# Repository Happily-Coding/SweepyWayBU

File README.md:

# SweepyWay Split Keyboard
A truly ergonomic, begginner friendly keyboard.

## Photos & Outputs

left side | right side
-|-
 | 

[More outputs](https://happily-coding.github.io/SweepyWay/) 
<!-- 
 | 
-->

## Features
* **Beginner friendly**
  * Abundant keys, but in non disruptive places.
* **Truly ergonomic**
  * Aggressive column stagger, like Ferris Sweep, to match how fingers are staggered.
  * Choc V1 keys
    * Very low actuation force switches available (example: nocturnal)
    * Low profile (seamless use without handrest, easier to adjust height without an adjustable desk)
    * ChocV1 spacing (reach the outer columns with less over-stretching)
  * Tenting, negative tilting, adjustable height and hand rest solutions
* **Energy efficient**
  * [Nice!nano](https://nicekeyboards.com/nice-nano) optimised, but any promicro should work (bottom up) 
  * [Nice!view](https://nicekeyboards.com/nice-view) support
  * No leds
* **Accident prepared** 
  * Controller far away from accidental splash zones,
  * Power switch for transport
  * No metal plates to help prevent static discharge from friying the keyboard
  * Hotswappable battery, switches, keycaps, controller, and case. Replace anything that breaks or you dislike.
    * You can even remove the components and use them with a different pcb.
* **Easy to modify** (Declarative design done via yaml)
  * Layout is declared using [Ergogen](https://github.com/mrzealot/ergogen/). 
  * Uses Ergogen to translate YAML to a KiCad PCB and plate files for FR-4 fab or laser cutting
  * Uses [kicad-automation-scripts](https://github.com/productize/kicad-automation-scripts) and [FreeRouting](https://github.com/freerouting/freerouting) to **automatically route the traces on the PCB**
  * Uses [KiKit](https://github.com/yaqwsx/KiKit) to render PCB previews and production-ready **Gerber files**

## Build Status

<!-- from original repo
## Todo
Mio:
Paso 1: mover todos los electronicos para arriba con mismo ofset
mcu_nice_nano
display_nice_view
battery_connector_jst_ph_2
reset_switch_tht_top
utility_ergogen_logo
version_txt
power_switch_smd_side
polygon arriba

Paso 2: sacar cosas raras/ tratar de simplificar el file

Paso 3:
hay que recrear el area, y reorganizar componentes como mi original
hay que recrear el outline y organizar componentes como el original (pero todavia no)

* Bottom Plate (Thick PCB with cutouts for all components placed at the bottom. Optimised for maximum thinness)
* Remove or document magic numbers
* SMD footrints
* Middle bracked PCB with touchpad (Holds both halves together rigidly)
* stabilizer cutouts Needs more research...
  Thanks https://github.com/jasonhazel for measuring the ChocFox WOB 3u spacebar stabilizer spacing. (40mm)
  watch https://www.youtube.com/watch?v=5tERUZ_BSPM
-->

## How to modify it
<!-- from original repo
### Add more keys in places that don't interfere with the controller
Add elements to the row or column matrix, and map them (WIP, TODO explain with more detail)

### Use other controllers

### Use mx switches / chocv2 switches

### Use other battery/reset switches/ footprints
See this examples: 
https://github.com/jsbursik/Janus-Keyboard mx nice nano reversible with custom footprints
https://github.com/tarneaux/triboard xiao controller choc spaced reversible with battery polygon!
https://github.com/Henkru/novum mx with jlpcb target, middle layer for stability, and awesome background art
https://github.com/Musab-Hassan/aurora_keyboard very detailed, and well organized mx example
https://github.com/soundmonster/samoklava/tree/main
https://github.com/christianselig/caldera-keyboard/blob/main/ergogen/config.yaml
https://github.com/jusdisgi/splaveferris/blob/main/ergogen/config.yaml (choc v1, smd) <-- reference for mirrored
https://github.com/jusdisgi/biggie-splays/blob/main/biggie-splays_choc_v1/config.yaml mirror matrix
https://pastebin.com/JzsmATYZ celoide reversible (obtianed from atreus/absolem discord) https://cdn.discordapp.com/attachments/759825860617437204/1376609916986327150/pleiades.yaml?ex=685b8624&is=685a34a4&hm=b6c63e79710fd8ff0cd410843348a5f8570dccdcfe2448ce519ddc2d7e60ecf4&
Complex case, and mounting example with celodie footpritns https://github.com/MalusKnight/SplitMax-Ergogen/blob/main/config.yaml and oleds
https://github.com/Nuclear-Squid/Quacken/blob/main/config.yaml [ro micro non celoide]
https://peterlyons.com/problog/2024/05/kipra-keyboard/ how to load an ergogen otuput to freecad 
https://github.com/johnlamb/LambBT/blob/main/ergogen/config.yaml case, m2 screwes, etc 
https://github.com/AtomicJon/jonkey/blob/main/jonkey-v2.yml other celoide footprints usage
https://github.com/scipioni/clavis alternative stup for auto routing 
#asym in theory can be used in outlines to get only mirrored or only normal points https://docs.ergogen.xyz/outlines/
-->

If you would like to modify this:
* fork it
* change `ergogen/config.yaml` to your liking
* reactivate github workflows
* reactivate github pages at https://github.com/your-name/your-repo/settings/pages, choose github actions instead of a branch
* push your changes; the `build.yml` GitHub Workflow will pick it up, autoroute and generate Gerbers, all in a zip file.
  See https://github.com/soundmonster/samoklava/actions
* or:
  * make sure to have Docker CLI and NodeJS installed
  * run `make setup clean all`
  * check the `output` folder for KiCad PCBs and Gerbers
* you can find the latest build artifacts [here](https://happily-coding.github.io/SweepyWay/)

See the [workflow](.github/workflows/build.yml) or the [Makefile](Makefile) for more details.

## Credits
- [mxooaar](https://www.reddit.com/r/ErgoMechKeyboards/comments/1lanvon/comment/mxooaar/) for peaking my interest in actually building my idea for a keyboard
- [christianselig caldera keyboard](https://github.com/christianselig/caldera-keyboard) for showing that creating a custom keyboard was reasonably easy
- [Ergogen](https://github.com/ergogen/ergogen) for the awesome tool for building most of the keyboard
- [Soundmonster Samaklova Keyboard](https://github.com/soundmonster/samoklava/tree/main) for automatic electronic routing
- [tbaumann typematrix](https://github.com/tbaumann/typematrix_split_new/tree/main/ergogen) for automatic documentation, and example of how to use celoide ergonomic footprints
- [Celoide](https://github.com/ceoloide/ergogen-footprints) for the library of additional ergogen footprints for more parts.

## Disclaimer
**Work in progress!**

## Important
Only connect battery if a nice!nano board is used!

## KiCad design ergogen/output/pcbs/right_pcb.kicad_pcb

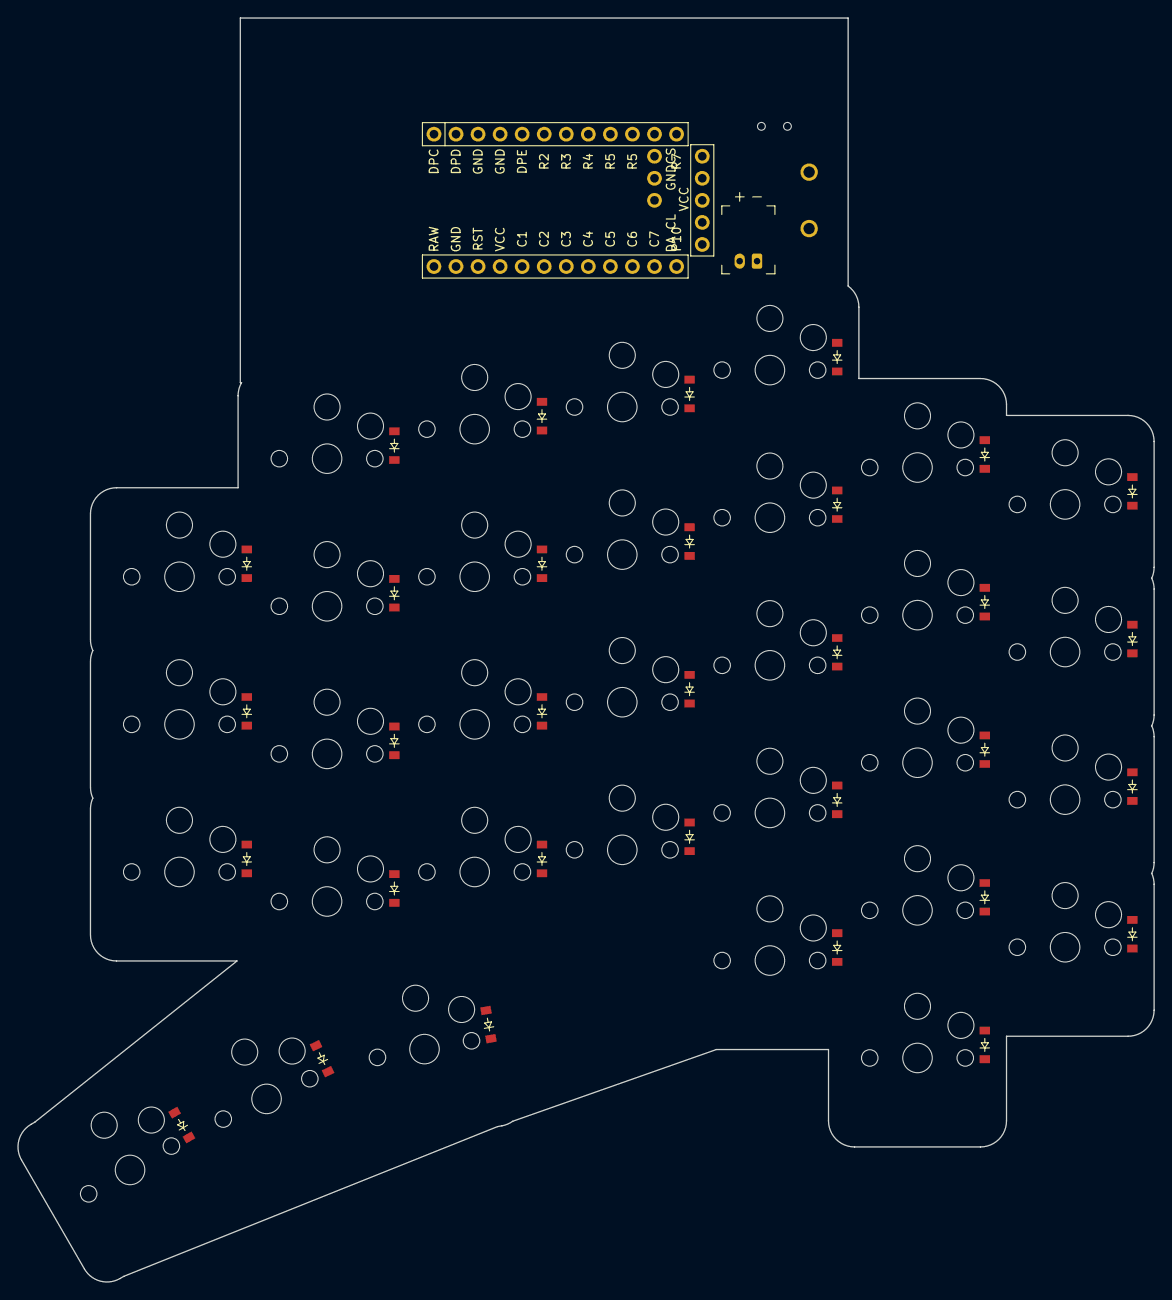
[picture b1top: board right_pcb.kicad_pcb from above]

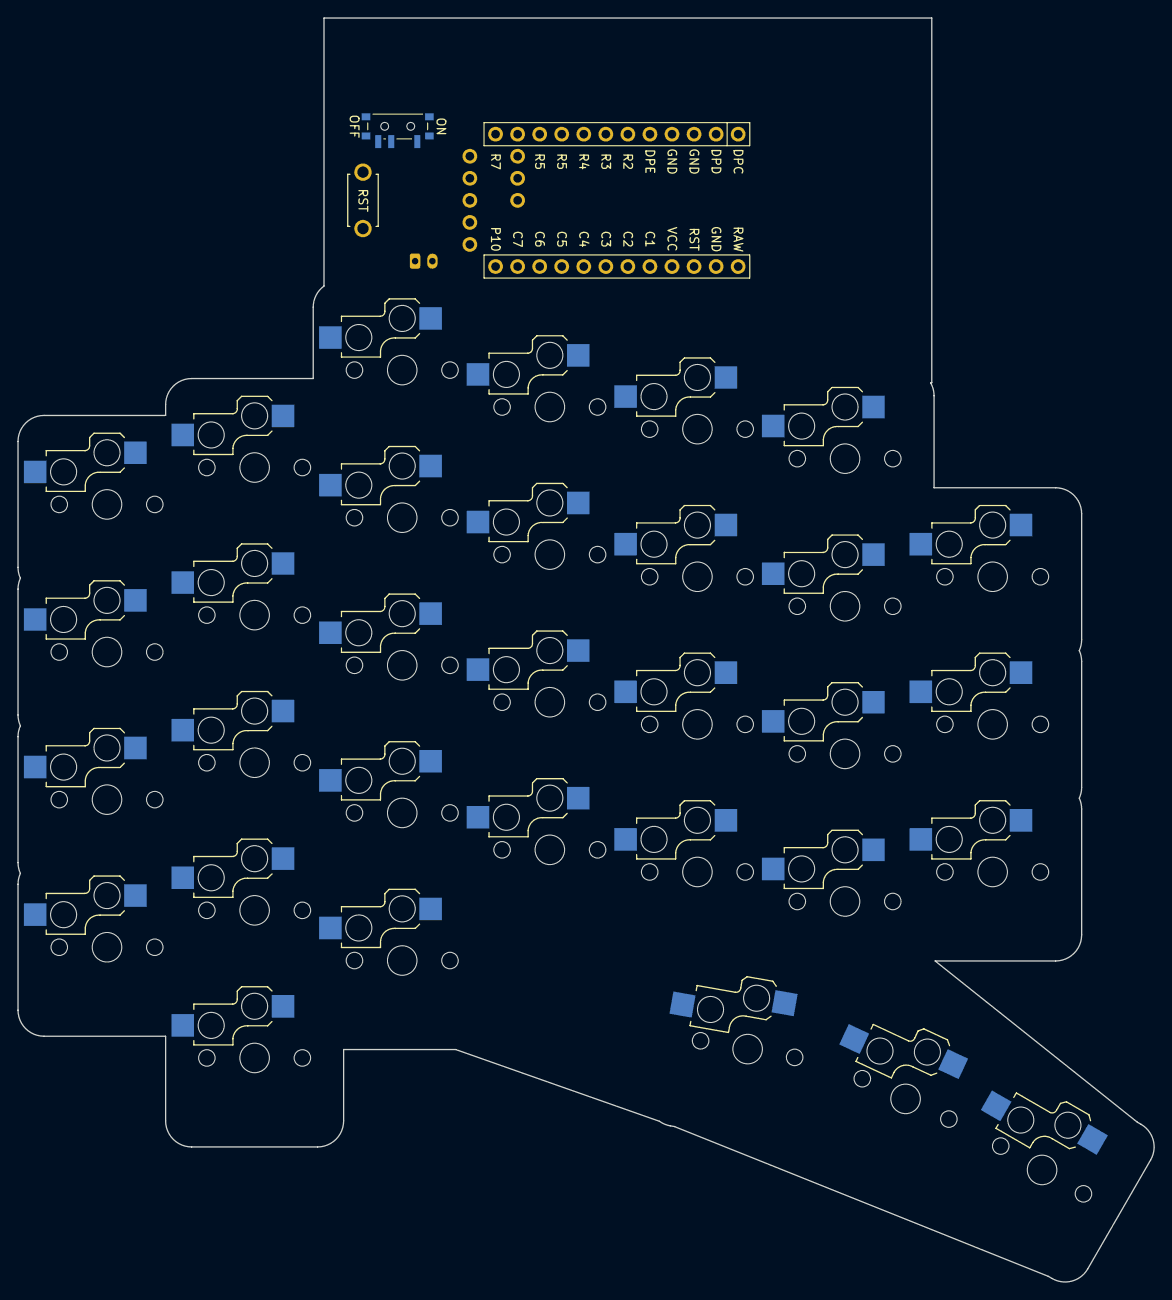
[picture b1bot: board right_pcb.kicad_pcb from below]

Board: 2 copper layers, 130.8 x 145.6 mm, 69 parts (34 on the bottom side), 52 nets, no tracks yet.

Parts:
D1, D2, D3, D4, D5, D6, D7, D8, D9, D10, D11, D12, D13, D14, D15, D16, D17, D18, D19, D20, D21, D22, D23, D24, D25, D26, D27, D28, D29, D30, D31, D32: diode_tht_sod123
DISP1: display_nice_view
JST1: battery_connector_jst_ph_2
MCU1: mcu_nice_nano
PWR1: power_switch_smd_side
RST1: reset_switch_tht_top
S1, S2, S3, S4, S5, S6, S7, S8, S9, S10, S11, S12, S13, S14, S15, S16, S17, S18, S19, S20, S21, S22, S23, S24, S25, S26, S27, S28, S29, S30, S31, S32: switch_choc_v1_v2

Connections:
BAT_P: JST1.2, PWR1.1
C1: MCU1.20, S1.2, S2.2, S3.2, S4.2
C2: MCU1.19, S5.2, S6.2, S7.2, S8.2, S9.2
C3: MCU1.18, S10.2, S11.2, S12.2, S13.2, S14.2
C4: MCU1.17, S15.2, S16.2, S17.2, S18.2
C5: MCU1.16, S19.2, S20.2, S21.2, S22.2
C6: MCU1.15, S23.2, S24.2, S25.2, S26.2
C7: MCU1.14, S27.2, S28.2, S29.2
DPC: DISP1.4, MCU1.1
DPD: DISP1.5, MCU1.2
DPE: DISP1.1, MCU1.5
GND: DISP1.2, JST1.1, MCU1.3, MCU1.4, MCU1.23, RST1.2
R1: D4.1, D9.1, D14.1, D18.1, D22.1, D26.1
R2: D3.1, D8.1, D13.1, D17.1, D21.1, D25.1, D29.1, MCU1.6
R3: D2.1, D7.1, D12.1, D16.1, D20.1, D24.1, D28.1, MCU1.7
R4: D1.1, D6.1, D11.1, D15.1, D19.1, D23.1, D27.1, MCU1.8
R5: D5.1, D10.1, D30.1, D31.1, D32.1, MCU1.9, MCU1.10
RAW: MCU1.24, PWR1.2
RST: MCU1.22, RST1.1
VCC: DISP1.3, MCU1.21
mirror_col1_row1: D4.2, S4.1
mirror_col1_row2: D3.2, S3.1
mirror_col1_row3: D2.2, S2.1
mirror_col1_row4: D1.2, S1.1
mirror_col1_thumb_row_1: D30.2, S30.1
mirror_col2_row1: D9.2, S9.1
mirror_col2_row2: D8.2, S8.1
mirror_col2_row3: D7.2, S7.1
mirror_col2_row4: D6.2, S6.1
mirror_col2_row5: D5.2, S5.1
mirror_col2_thumb_row_1: D31.2, S31.1
mirror_col3_row1: D14.2, S14.1
mirror_col3_row2: D13.2, S13.1
mirror_col3_row3: D12.2, S12.1
mirror_col3_row4: D11.2, S11.1
mirror_col3_row5: D10.2, S10.1
mirror_col3_thumb_row_1: D32.2, S32.1
mirror_col4_row1: D18.2, S18.1
mirror_col4_row2: D17.2, S17.1
mirror_col4_row3: D16.2, S16.1
mirror_col4_row4: D15.2, S15.1
mirror_col5_row1: D22.2, S22.1
mirror_col5_row2: D21.2, S21.1
mirror_col5_row3: D20.2, S20.1
mirror_col5_row4: D19.2, S19.1
mirror_col6_row1: D26.2, S26.1
mirror_col6_row2: D25.2, S25.1
mirror_col6_row3: D24.2, S24.1
mirror_col6_row4: D23.2, S23.1
mirror_col7_row2: D29.2, S29.1
mirror_col7_row3: D28.2, S28.1
mirror_col7_row4: D27.2, S27.1

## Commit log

2025-06-28 rolled back to almost working pdf commit
2025-06-28 Debug change
2025-06-28 commented pdf creation
2025-06-28 Reverted changes
